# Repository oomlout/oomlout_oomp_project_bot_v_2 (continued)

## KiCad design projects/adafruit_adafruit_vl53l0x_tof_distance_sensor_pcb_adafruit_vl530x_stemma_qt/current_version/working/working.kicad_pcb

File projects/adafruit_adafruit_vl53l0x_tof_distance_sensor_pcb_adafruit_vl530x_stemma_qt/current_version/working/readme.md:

# adafruit_vl53l0x_tof_distance_sensor_pcb
 
## summary 
* id: adafruit_adafruit_vl53l0x_tof_distance_sensor_pcb_adafruit_vl530x_stemma_qt
* user: adafruit
* name: adafruit_vl53l0x_tof_distance_sensor_pcb
* board: adafruit_vl530x_stemma_qt
* repo: https://github.com/adafruit/Adafruit-VL53L0X-ToF-Distance-Sensor-PCB

* src_file_repo_sch: 
* src_file_repo_sch_link: https://github.com/adafruit/Adafruit-VL53L0X-ToF-Distance-Sensor-PCB/tree/master/
* full details link: https://github.com/oomlout/oomlout_oomp_project_bot_v_2/tree/main/projects/adafruit_adafruit_vl53l0x_tof_distance_sensor_pcb_adafruit_vl530x_stemma_qt/current_version/working  

## schematic  
  
[schematic (pdf)](working_schematic.pdf) 

## pcb  

[board (pdf)](working.pdf)  

## working_bom
| Id | Designator | Footprint | Quantity | Designation | Supplier and ref |  | None | 
| --- | --- | --- | --- | --- | --- | --- | --- | 
| 1 | C5,C4 | 0805-NO | 2 | 10uF |  |  | [''] | 
| 2 | U$36 | ADAFRUIT_3.5MM | 1 |  |  |  | [''] | 
| 3 | R2,R1,R3 | 0603-NO | 3 | 10K |  |  | [''] | 
| 4 | U3 | SOT23-5 | 1 | LP5907-2.8 |  |  | [''] | 
| 5 | C6 | 0603-NO | 1 | 0.1uF |  |  | [''] | 
| 6 | D2 | CHIPLED_0603_NOOUTLINE | 1 | GREEN |  |  | [''] | 
| 7 | U$34,U$33,U$30,U$31 | MOUNTINGHOLE_2.5_PLATED | 4 | MOUNTINGHOLE2.5 |  |  | [''] | 
| 8 | U1 | LGA12_ST | 1 | VL53L0X |  |  | [''] | 
| 9 | D1 | SOD-323 | 1 | 1N4148 |  |  | [''] | 
| 10 | R7 | RESPACK_4X0603 | 1 | 10K |  |  | [''] | 
| 11 | Q3 | SOT363 | 1 | BSS138 |  |  | [''] | 
| 12 | JP2 | 1X06_ROUND_70 | 1 |  |  |  | [''] | 
| 13 | CONN4,CONN3 | JST_SH4 | 2 | STEMMA_I2C_QT |  |  | [''] | 
| 14 | FID1,FID4 | FIDUCIAL_1MM | 2 | FIDUCIAL_1MM |  |  | [''] | 
| 15 | U$39,U$38 | STEMMAQT | 2 |  |  |  | [''] | 
| 16 | U$37 | PCBFEAT-REV-040 | 1 |  |  |  | [''] | 

## bom_schematic
| Ref | Qnty | Value | Cmp name | Footprint | Description | Vendor | DNP | 
| --- | --- | --- | --- | --- | --- | --- | --- | 
| C4, C5 | 2 | 10uF | CAP_CERAMIC0805-NOOUTLINE | working:0805-NO |  |  |  | 
| C6 | 1 | 0.1uF | CAP_CERAMIC0603_NO | working:0603-NO |  |  |  | 
| CONN3, CONN4 | 2 | STEMMA_I2C_QT | STEMMA_I2C_QT | working:JST_SH4 |  |  |  | 
| D1 | 1 | 1N4148 | DIODESOD-323 | working:SOD-323 |  |  |  | 
| D2 | 1 | GREEN | LED0603_NOOUTLINE | working:CHIPLED_0603_NOOUTLINE |  |  |  | 
| FID1, FID4 | 2 | FIDUCIAL_1MM | FIDUCIAL_1MM | working:FIDUCIAL_1MM |  |  |  | 
| JP2 | 1 | HEADER-1X670MIL | HEADER-1X670MIL | working:1X06_ROUND_70 |  |  |  | 
| Q3 | 1 | BSS138 | MOSFET-N_DUAL | working:SOT363 |  |  |  | 
| R1, R2, R3 | 3 | 10K | RESISTOR_0603_NOOUT | working:0603-NO |  |  |  | 
| R7 | 1 | 10K | RESISTOR_4PACK | working:RESPACK_4X0603 |  |  |  | 
| U1 | 1 | VL53L0X | VL53L0X | working:LGA12_ST |  |  |  | 
| U3 | 1 | LP5907-2.8 | VREG_SOT23-5 | working:SOT23-5 |  |  |  | 
| U$30, U$31, U$33, U$34 | 4 | MOUNTINGHOLE2.5 | MOUNTINGHOLE2.5 | working:MOUNTINGHOLE_2.5_PLATED |  |  |  | 

## mounting_holes
| x | y | package | value | ref | size | 
| --- | --- | --- | --- | --- | --- | 
| 0.0 | 12.7 | MOUNTINGHOLE_2.5_PLATED | MOUNTINGHOLE2.5 | U$30 | m3 | 
| 20.32 | 12.7 | MOUNTINGHOLE_2.5_PLATED | MOUNTINGHOLE2.5 | U$31 | m3 | 
| 0.0 | 0.0 | MOUNTINGHOLE_2.5_PLATED | MOUNTINGHOLE2.5 | U$33 | m3 | 
| 20.32 | 0.0 | MOUNTINGHOLE_2.5_PLATED | MOUNTINGHOLE2.5 | U$34 | m3 |

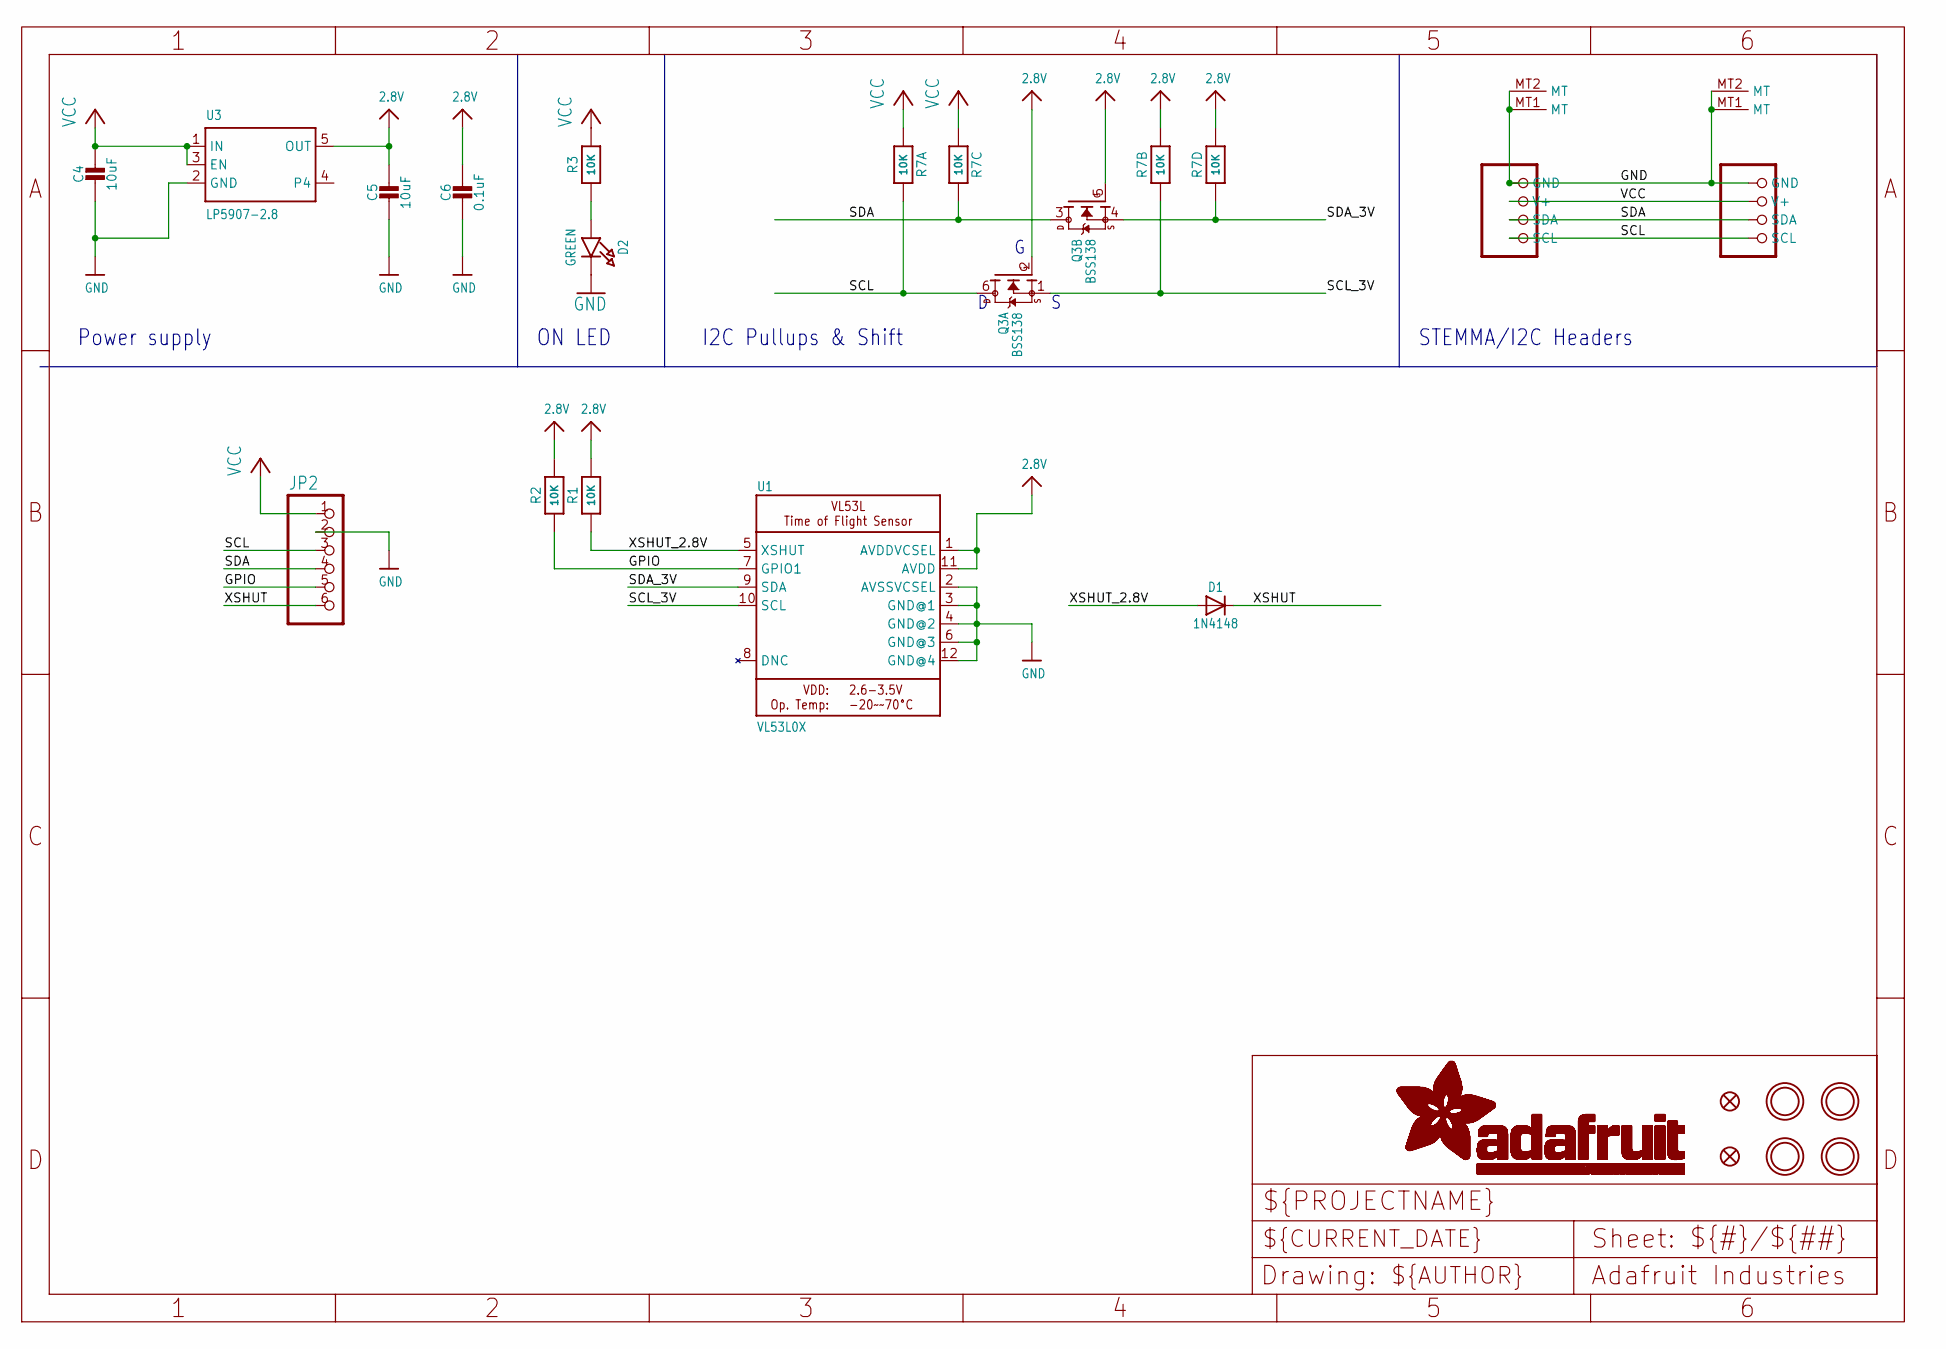
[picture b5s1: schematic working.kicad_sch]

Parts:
C4, C5: 10uF; 0805-NO
C6: 0.1uF; 0603-NO
CONN3, CONN4: STEMMA_I2C_QT; JST_SH4
D1: 1N4148; SOD-323
D2: GREEN; CHIPLED_0603_NOOUTLINE
FID1, FID4: FIDUCIAL_1MM
JP2: HEADER-1X670MIL; 1X06_ROUND_70
Q3: BSS138; SOT363
R1, R2, R3: 10K; 0603-NO
R7: 10K; RESPACK_4X0603
U1: VL53L0X; LGA12_ST
U3: LP5907-2.8; SOT23-5
U$30, U$31, U$33, U$34: MOUNTINGHOLE2.5; MOUNTINGHOLE_2.5_PLATED

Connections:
2.8V: C5.1, C6.1, Q3.2 (G), Q3.5 (G), R1.2, R2.2, R7.2 (1), R7.4 (1), U1.1 (AVDDVCSEL), U1.11 (AVDD), U3.5 (OUT)
GND: C4.2, C5.2, C6.2, CONN3.1 (GND), CONN3.MT1 (MT), CONN3.MT2 (MT), CONN4.1 (GND), CONN4.MT1 (MT), CONN4.MT2 (MT), D2.C, JP2.2, U1.2 (AVSSVCSEL), U1.3 (GND@1), U1.4 (GND@2), U1.6 (GND@3), U1.12 (GND@4), U3.2 (GND)
GPIO: JP2.5, R2.1, U1.7 (GPIO1)
unnamed: D2.A, R3.1
SCL: CONN3.4 (SCL), CONN4.4 (SCL), JP2.3, Q3.6 (D), R7.8 (2)
SCL_3V: Q3.1 (S), R7.7 (2), U1.10 (SCL)
SDA: CONN3.3 (SDA), CONN4.3 (SDA), JP2.4, Q3.3 (D), R7.6 (2)
SDA_3V: Q3.4 (S), R7.5 (2), U1.9 (SDA)
VCC: C4.1, CONN3.2 (V+), CONN4.2 (V+), JP2.1, R3.2, R7.1, R7.3 (1), U3.1 (IN), U3.3 (EN)
XSHUT: D1.C, JP2.6
XSHUT_2.8V: D1.A, R1.1, U1.5 (XSHUT)

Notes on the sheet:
I2C Pullups & Shift
Power supply
ON LED
STEMMA/I2C Headers

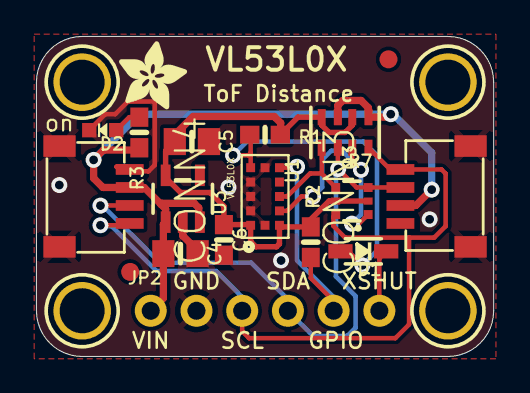
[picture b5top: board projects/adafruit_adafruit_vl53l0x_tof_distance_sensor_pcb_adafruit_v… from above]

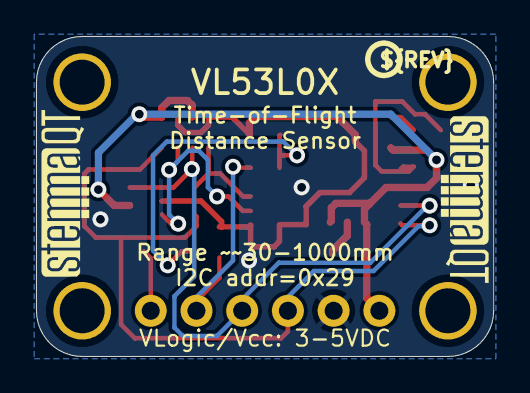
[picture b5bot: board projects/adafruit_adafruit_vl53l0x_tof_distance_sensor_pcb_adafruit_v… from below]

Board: 2 copper layers, 25.4 x 17.8 mm, 25 parts (3 on the bottom side), 11 nets.

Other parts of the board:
U$36: ADAFRUIT_3.5MM
U$37: PCBFEAT-REV-040
U$38, U$39: STEMMAQT
